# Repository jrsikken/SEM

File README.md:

# SEM
A tiny board with AEM10330 solar harvesting IC and regulated output

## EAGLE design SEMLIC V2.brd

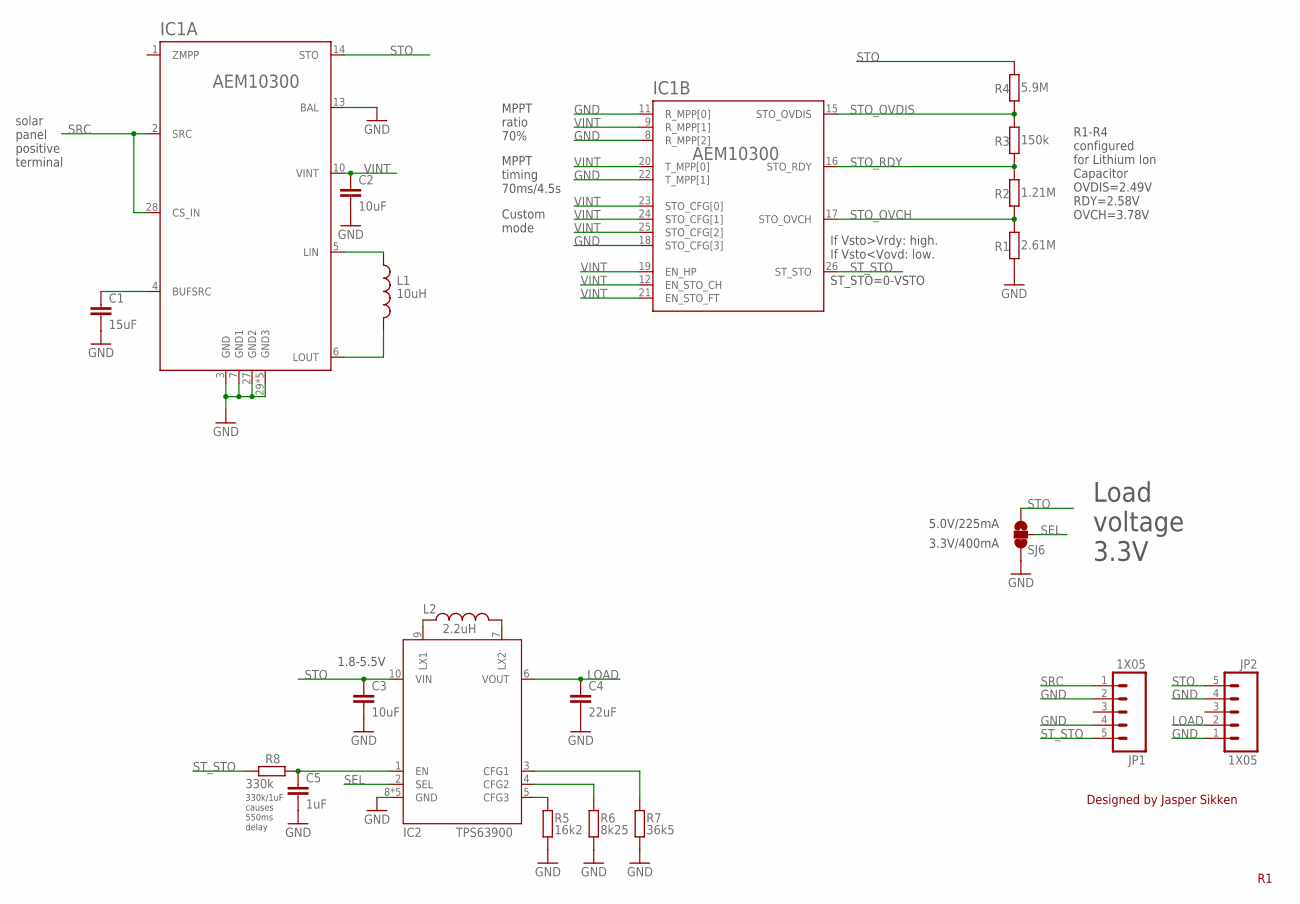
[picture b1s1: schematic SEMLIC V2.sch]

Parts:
C1: 15uF; C0402
C2: 10uF; C0402
C3: 10uF; C0603
C4: 22uF; C0603
C5: 1uF; C0402
IC1: AEM10300; QFN28P4X4
IC2: TPS63900; WSON10
JP1, JP2: 1X05; 1X05_2.54MM_ROUND_NOSILK
L1: 10uH; L_1008_[2520]
L2: 2.2uH; L_1008_[2520]
R1: 2.61M; R0402
R2: 1.21M; R0402
R3: 150k; R0402
R4: 5.9M; R0402
R5: 16k2; R0402
R6: 8k25; R0402
R7: 36k5; R0402
R8: 330k; R0402
SJ6: SOLDERJUMPER_3WAY_12SHORT3WAY; SJ_3S_NC_0402

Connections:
BUFSRC: C1.1, IC1.4 (BUFSRC)
GND: C1.2, C2.2, C3.2, C4.2, C5.2, IC1.3 (GND), IC1.7 (GND1), IC1.8 (R_MPP[2]), IC1.11 (R_MPP[0]), IC1.13 (BAL), IC1.18 (STO_CFG[3]), IC1.22 (T_MPP[1]), IC1.27 (GND2), IC1.29 (GND3), IC1.P$1 (GND3), IC1.P$2 (GND3), IC1.P$3 (GND3), IC1.P$4 (GND3), IC2.8 (GND), IC2.29 (GND), IC2.P$2 (GND), IC2.P$4 (GND), IC2.P$5 (GND), JP1.2, JP1.4, JP2.1, JP2.4, R1.1, R5.2, R6.2, R7.2, SJ6.1
LIN: IC1.5 (LIN), L1.1
LOAD: C4.1, IC2.6 (VOUT), JP2.2
LOUT: IC1.6 (LOUT), L1.2
unnamed: IC2.9 (LX1), L2.1
unnamed: IC2.7 (LX2), L2.2
unnamed: IC2.5 (CFG3), R5.1
unnamed: IC2.4 (CFG2), R6.1
unnamed: IC2.3 (CFG1), R7.1
SEL: IC2.2 (SEL), SJ6.2
SRC: IC1.2 (SRC), IC1.28 (CS_IN), JP1.1
STO: C3.1, IC1.14 (STO), IC2.10 (VIN), JP2.5, R4.2, SJ6.3
STO_OVCH: IC1.17 (STO_OVCH), R1.2, R2.1
STO_OVDIS: IC1.15 (STO_OVDIS), R3.2, R4.1
STO_RDY: IC1.16 (STO_RDY), R2.2, R3.1
ST_STO: IC1.26 (ST_STO), JP1.5, R8.2
TPS_EN: C5.1, IC2.1 (EN), R8.1
VINT: C2.1, IC1.9 (R_MPP[1]), IC1.10 (VINT), IC1.12 (EN_STO_CH), IC1.19 (EN_HP), IC1.20 (T_MPP[0]), IC1.21 (EN_STO_FT), IC1.23 (STO_CFG[0]), IC1.24 (STO_CFG[1]), IC1.25 (STO_CFG[2])

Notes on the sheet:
Designed by Jasper Sikken
solar panel positive terminal
3.3V/400mA
ST_STO=0-VSTO
If Vsto>Vrdy: high. If Vsto<Vovd: low.
Load voltage 3.3V
R1-R4 configured for Lithium Ion Capacitor OVDIS=2.49V RDY=2.58V OVCH=3.78V
330k/1uF causes 550ms delay
1.8-5.5V
5.0V/225mA
Custom mode
MPPT ratio 70%
MPPT timing 70ms/4.5s

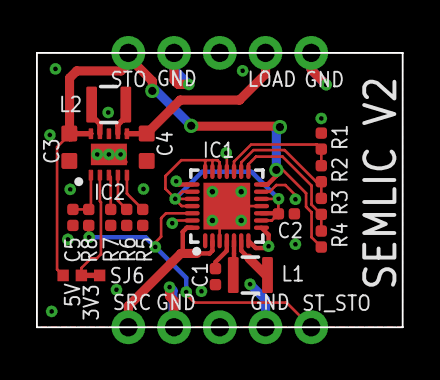
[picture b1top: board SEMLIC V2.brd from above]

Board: 2 copper layers, 20.3 x 15.2 mm, 20 parts (0 on the bottom side), 19 nets.

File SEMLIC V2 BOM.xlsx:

Qty | Value | Parts | Description | MF | MPN | have
1 | 15uF | C1 | Cap 6.3v X5R 15uF 20% 0402 | MURATA | GRM155R60J156ME05 | 8
1 | 10uF | C2 | Cap 10 μF, 6.3V, 20%, X5R 0402 | MURATA | CC0402MRX5R5BB106 | 8
1 | 10uF | C3 | Cap 10 μF, 10V, 20%, X5R, 0603 |  |  | 220
1 | 22uF | C4 | Cap 22uF, 10V, 20%, X5R, 0603 |  |  | 220
1 | 1uF | C5 | Cap 1uF, 10V, X5R, 20%, 0402 |  |  | 18
1 | AEM10300 | IC1 | Energy harvesting PMIC | E-peas | AEM10300 | 4
1 | TPS63900 | IC2 | Buck boost PMIC | Texas Instruments | TPS63900 | 220
1 | 10uH | L1 | Inductor 10uH 20% 1MHz 0.9A 0.6Ohm | MURATA | DFE252010F-100M | 9
1 | 2.61M | R1 | Res 2.61M 0402 1% |  |  | 50
1 | 1.21M | R2 | Res 1.21M 0402 1% |  |  | 30
1 | 150k | R3 | Res 150k 0402 1% |  |  | 220
1 | 5.9M | R4 | Res 5.9M 0402 1% |  |  | 40
1 | 16k2 | R5 | 16k2 0402 1% 200ppm |  |  | 220
1 | 8k25 | R6 | 8k25 0402 1% 200ppm |  |  | 220
1 | 36k5 | R7 | 36k5 0402 1% 200ppm |  |  | 220
1 | 330k | R8 | Res 330k 0402 1% |  |  | 220
1 | 2.2uH | L2 | Inductor 2.2uH 20% 1MHz 2.3A 0.082Ohm |  | DFE252012F-2R2M=P2 | 220

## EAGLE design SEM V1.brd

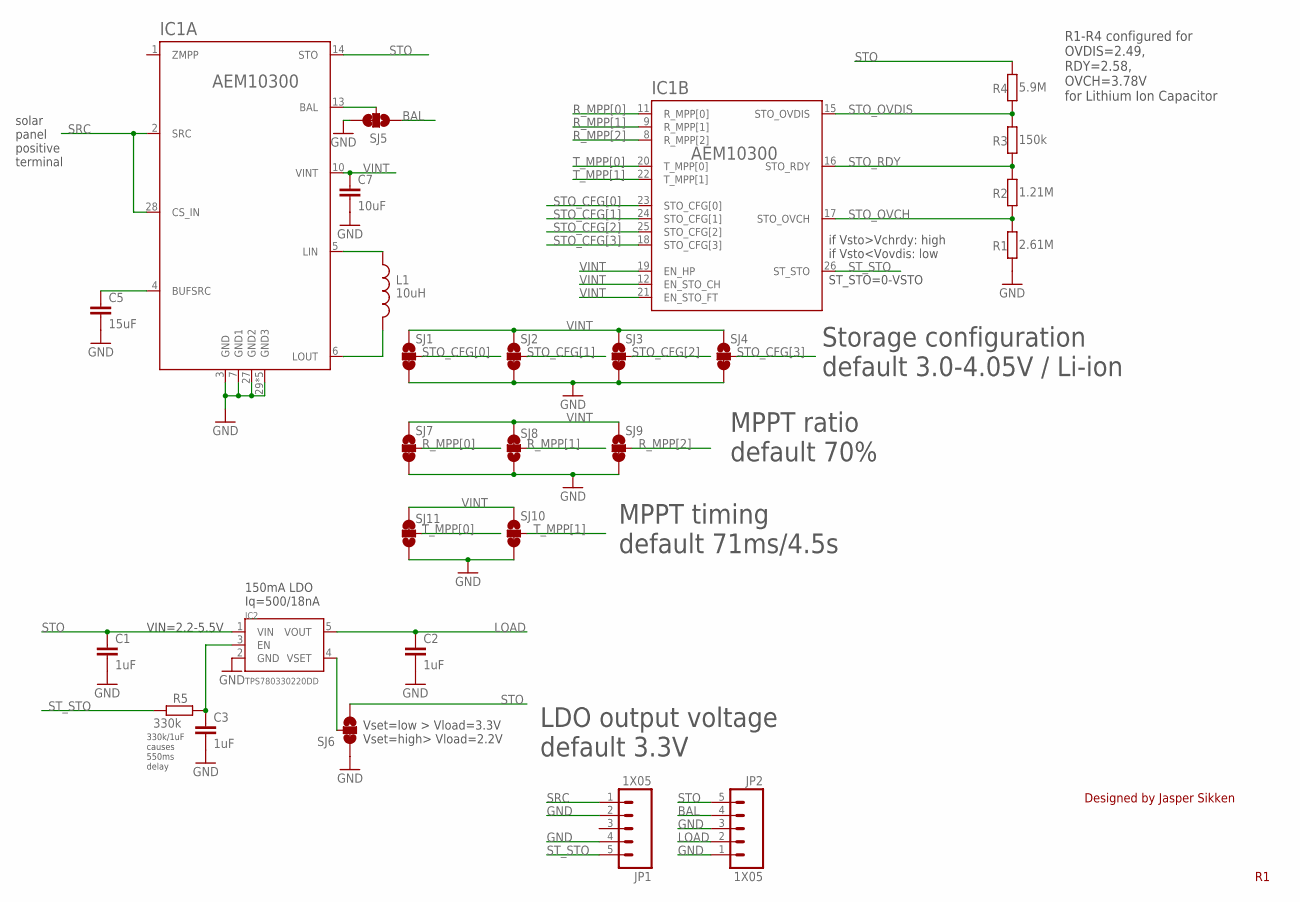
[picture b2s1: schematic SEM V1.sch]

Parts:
C1, C2, C3: 1uF; C0402
C5: 15uF; C0402
C7: 10uF; C0402
IC1: AEM10300; QFN28P4X4
IC2: TPS780330220DD; SOT23-5
JP1, JP2: 1X05; 1X05_2.54MM_ROUND_NOSILK
L1: 10uH; L_1008_[2520]
R1: 2.61M; R0402
R2: 1.21M; R0402
R3: 150k; R0402
R4: 5.9M; R0402
R5: 330k; R0402
SJ1, SJ2, SJ3, SJ4, SJ5, SJ6, SJ7, SJ8, SJ9, SJ10, SJ11: SOLDERJUMPER_3WAY_12SHORT3WAY; SJ_3S_NC_0402

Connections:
AEM_BAL: IC1.13 (BAL), SJ5.2
BAL: JP2.4, SJ5.3
BUFSRC: C5.1, IC1.4 (BUFSRC)
EN: C3.1, IC2.3 (EN), R5.1
GND: C1.2, C2.2, C3.2, C5.2, C7.2, IC1.3 (GND), IC1.7 (GND1), IC1.27 (GND2), IC1.29 (GND3), IC1.P$1 (GND3), IC1.P$2 (GND3), IC1.P$3 (GND3), IC1.P$4 (GND3), IC2.2 (GND), JP1.2, JP1.4, JP2.1, JP2.3, R1.1, SJ1.1, SJ2.1, SJ3.1, SJ4.1, SJ5.1, SJ6.1, SJ7.1, SJ8.3, SJ9.1, SJ10.1, SJ11.3
LIN: IC1.5 (LIN), L1.1
LOAD: C2.1, IC2.5 (VOUT), JP2.2
LOUT: IC1.6 (LOUT), L1.2
R_MPP[0]: IC1.11 (R_MPP[0]), SJ7.2
R_MPP[1]: IC1.9 (R_MPP[1]), SJ8.2
R_MPP[2]: IC1.8 (R_MPP[2]), SJ9.2
SRC: IC1.2 (SRC), IC1.28 (CS_IN), JP1.1
STO: C1.1, IC1.14 (STO), IC2.1 (VIN), JP2.5, R4.2, SJ6.3
STO_CFG[0]: IC1.23 (STO_CFG[0]), SJ1.2
STO_CFG[1]: IC1.24 (STO_CFG[1]), SJ2.2
STO_CFG[2]: IC1.25 (STO_CFG[2]), SJ3.2
STO_CFG[3]: IC1.18 (STO_CFG[3]), SJ4.2
STO_OVCH: IC1.17 (STO_OVCH), R1.2, R2.1
STO_OVDIS: IC1.15 (STO_OVDIS), R3.2, R4.1
STO_RDY: IC1.16 (STO_RDY), R2.2, R3.1
ST_STO: IC1.26 (ST_STO), JP1.5, R5.2
T_MPP[0]: IC1.20 (T_MPP[0]), SJ11.2
T_MPP[1]: IC1.22 (T_MPP[1]), SJ10.2
VINT: C7.1, IC1.10 (VINT), IC1.12 (EN_STO_CH), IC1.19 (EN_HP), IC1.21 (EN_STO_FT), SJ1.3, SJ2.3, SJ3.3, SJ4.3, SJ7.3, SJ8.1, SJ9.3, SJ10.3, SJ11.1
VSET: IC2.4 (VSET), SJ6.2

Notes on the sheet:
Designed by Jasper Sikken
solar panel positive terminal
MPPT ratio default 70%
150mA LDO Iq=500/18nA
Vset=low > Vload=3.3V Vset=high> Vload=2.2V
VIN=2.2-5.5V
ST_STO=0-VSTO
if Vsto>Vchrdy: high if Vsto<Vovdis: low
Storage configuration default 3.0-4.05V / Li-ion
MPPT timing default 71ms/4.5s
LDO output voltage default 3.3V
R1-R4 configured for OVDIS=2.49, RDY=2.58, OVCH=3.78V for Lithium Ion Capacitor
330k/1uF causes 550ms delay

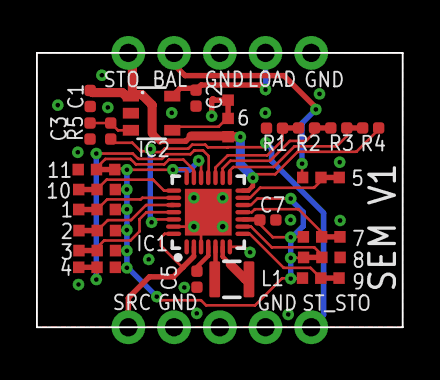
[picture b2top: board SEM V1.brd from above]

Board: 2 copper layers, 20.3 x 15.2 mm, 26 parts (0 on the bottom side), 25 nets.
